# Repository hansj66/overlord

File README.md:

# Overlord Robot Controller

## Overview

"Overlord" is a carrier board for the Raspberry Pi Compute module 5. The board facilitates easy integration with [Xiaomi Cybergear](https://www.mi.com/cyber-gear) motors and half duplex Dynamixels, like the [AX-12A](https://emanual.robotis.com/docs/en/dxl/ax/ax-12a/), [MX-12W](https://emanual.robotis.com/docs/en/dxl/ax/ax-12a/) servos.

The carrier board has an onboard can controller, can transciever, a 9 axis IMU with 100Hz sensor fusion, half duplex line driver circuitry for Dynamixel servos and has an acceptable power input range from 5 to 36V.

This repository contains:
* All the necessary KiCad schematics, PCB layout and gerber files for making copies of the carrier board.
* boot/firmware/config.txt (for the necessary boot overlays and IO mappings).
* Go code examples for communicating with Dynamixels, Cybergears and the IMU.
* Go code examples for how to implement remote control via a bluetooth gamepad, FrSky [XSR-SIM](https://www.frsky-rc.com/product/xsr-sim/) (or similar HID device).

## Licensing
This is open hardware and software. Licensing terms can be found [here](LICENSE.md).

## Getting started

In addition to the carrier board, you will need a 
* [Compute module 5](https://datasheets.raspberrypi.com/cm5/cm5-datasheet.pdf). 
* [Raspberry Pi Development Kit for Compute Module 5](https://www.raspberrypi.com/products/cm5-dev-kit/)
* If you plan to use wifi, I strongly suggest getting the official Raspberry Pi Compute module 4/5 antenna kit.
* A passive or active cooler for the CM5. If using an active cooler, attach the FAN connector to the "COOLER" socket on the carrier board.

### Programming the CM5

1. The compute module has to be flashed with an operating system before it can be used. Information on how to do this is available in the ["Compute Module Hardware"](https://www.raspberrypi.com/documentation/computers/compute-module.html#flash-compute-module-emmc) section on the offical [raspberrypi.com](https://www.raspberrypi.com/) site. Remember to enable SSH in the OS customisation settings before flashing the module.
1. Mount the CM5 in the carrier board and attach a battery or power supply to the "COMPUTE POWAH" port. Observe polarity. There is no reverse polarity protection circuitry. Reversing polarity will in all likelyhood fry the carrier board.
1. The blue LED on the carrier board will light up, indicating that it has 5V power. 
1. The CM5 will require a few seconds to boot before you can ssh in. (Tip: create an .ssh folder under the CM5 home folder and copy your public key to ./ssh/authorized_keys. You can then "ssh hostname" without having to type in a password)
1. The compute module will announce itself on the network. Given a "hostname", you should now be able to "ssh hostname" to get shell access.
1. Once you have shell access, run "sudo raspi-config" to enable i2c, spi and UART (enable serial port hardware, but not serial shell).
1. Now you can "sudo vi /boot/firmware/config.txt. Update the config.txt according to the [config.txt](./config/config.txt) in this repository. 
1. Run "sudo reboot now" to reboot the module. This makes sure that the correct overlays are loaded and that the GPIO mappings are correct.

You are now all set to start playing around with the board.

## Configuration and code examples

* [Remote control](./firmware/examples/remote-control/README.md)
* [Dynamixel](./firmware/examples/dynamixel/README.md)
* [Xiaomi Cybergear](./firmware/examples/cybergear/README.MD)
* [IMU](./firmware/examples/imu/README.md)

## Networking

This board was designed for simplicity and ease of use with the primary goal being actuator control and balancing. Apart from the onboard IMU, there is no sensing or GPIO access. It is however possible to directly connect the board to another Pi or any other board that supports Auto MDI-X directly using a standard ethernet cable. Access to GPIO, camera etc can then be implemented via a simple tcp client/server.

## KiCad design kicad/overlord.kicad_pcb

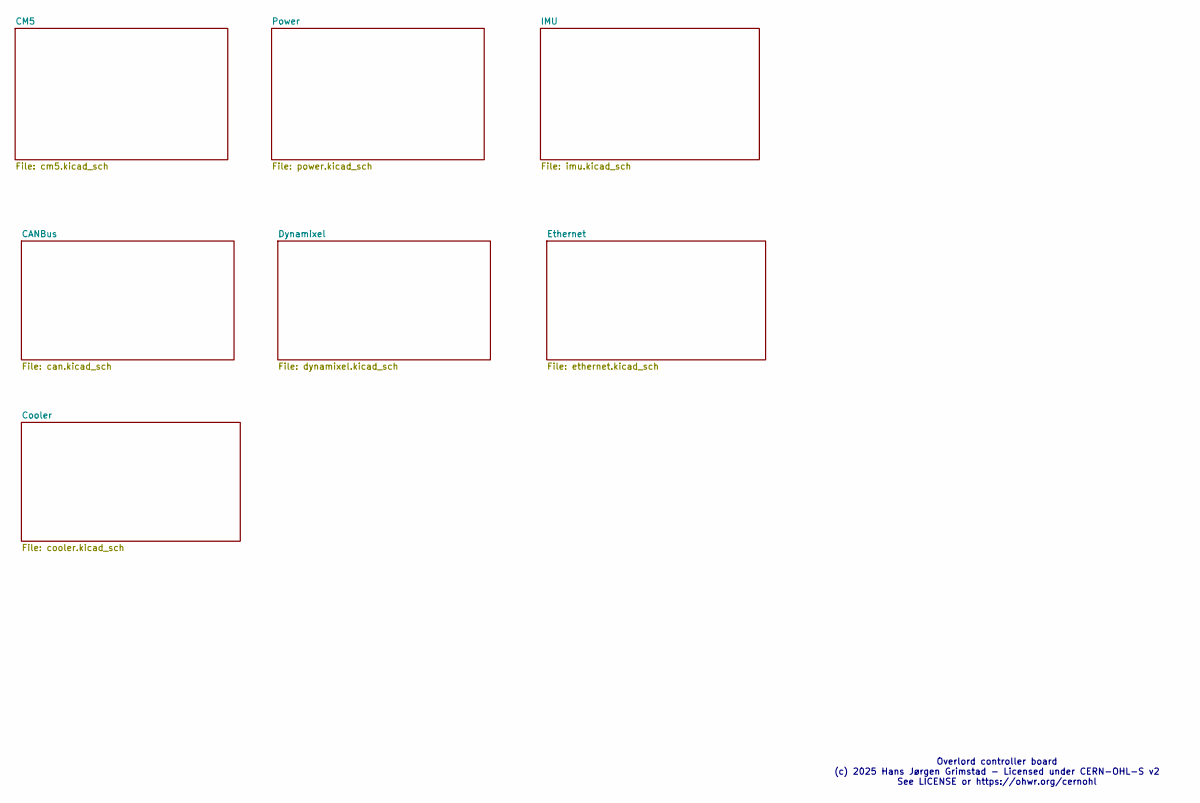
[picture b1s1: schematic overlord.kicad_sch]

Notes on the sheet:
Overlord controller board (c) 2025 Hans Jørgen Grimstad - Licensed under CERN-OHL-S v2 See LICENSE or https://ohwr.org/cernohl

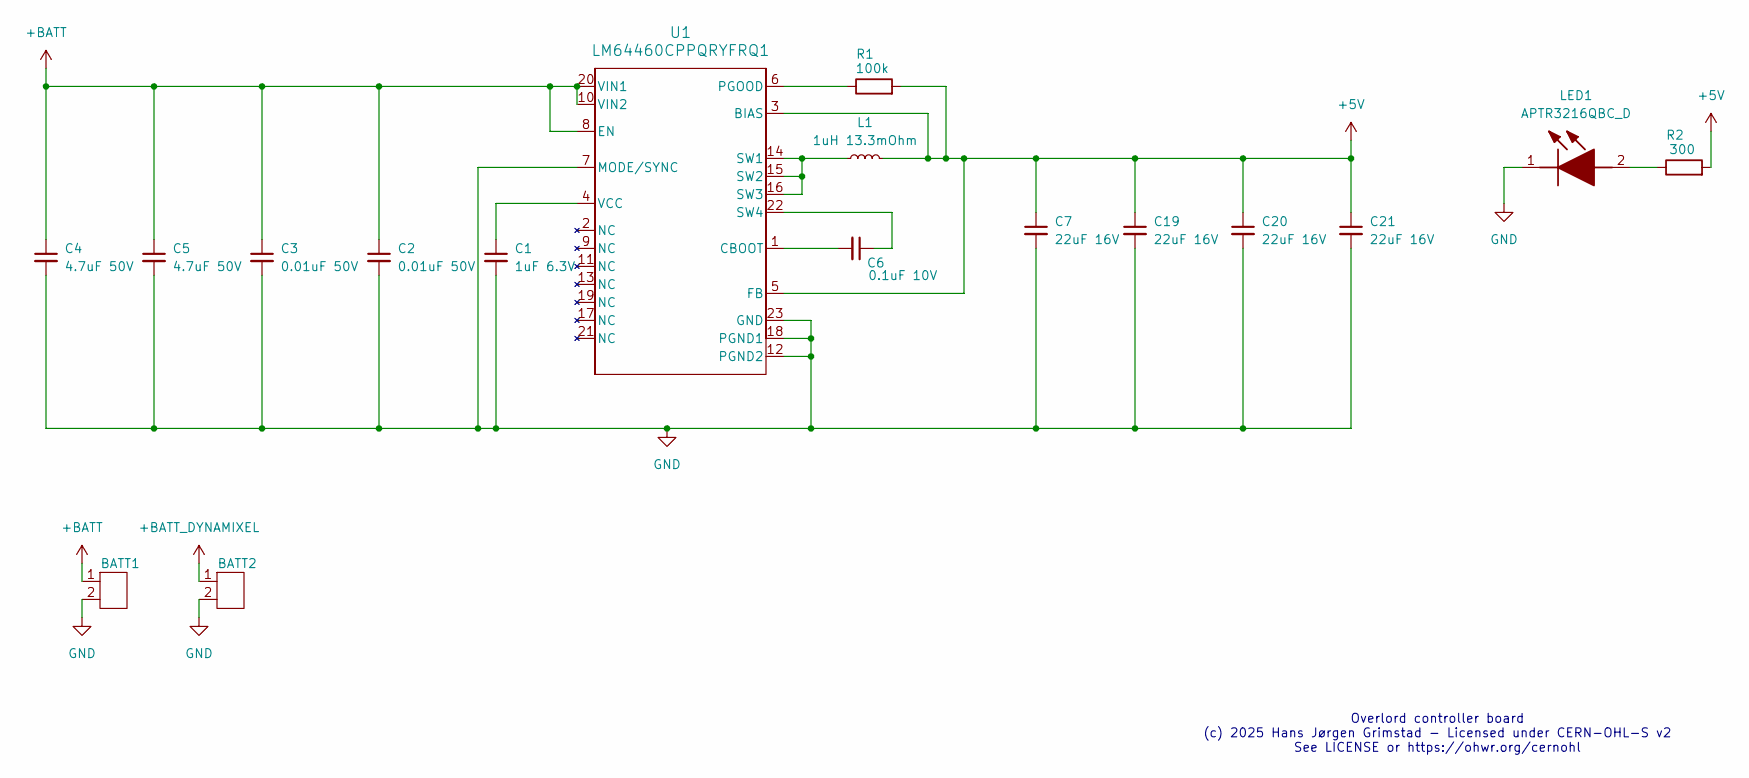
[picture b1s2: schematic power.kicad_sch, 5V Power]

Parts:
BATT1, BATT2: MOLEX-39531-5002
C1: 1uF 6.3V; C_0603_1608Metric
C2, C3: 0.01uF 50V; C_0402_1005Metric
C4, C5: 4.7uF 50V; C_1206_3216Metric
C6: 0.1uF 10V; C_0402_1005Metric
C7, C19, C20, C21: 22uF 16V; C_1210_3225Metric
L1: 1uH 13.3mOhm; L_Coilcraft_XAL4020-XXX
LED1: APTR3216QBC_D; LED_1206_3216Metric; Mouser Part Number 604-APTR3216QBC/D
R1: 100k; R_0402_1005Metric
R2: 300; R_0402_1005Metric
U1: LM64460CPPQRYFRQ1; VQFN22_RYF_TEX

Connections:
+5V: C7.1, C19.1, C20.1, C21.1, L1.2, R1.2, R2.2, U1.3 (BIAS), U1.5 (FB); also elsewhere on the board
+BATT: BATT1.1, C2.1, C3.1, C4.1, C5.1, U1.8 (EN), U1.10 (VIN2), U1.20 (VIN1)
+BATT_DYNAMIXEL: BATT2.1; also elsewhere on the board
GND: BATT1.2, BATT2.2, C1.2, C2.2, C3.2, C4.2, C5.2, C7.2, C19.2, C20.2, C21.2, U1.7 (MODE/SYNC), U1.12 (PGND2), U1.18 (PGND1), U1.23 (GND); also elsewhere on the board
unnamed 35: LED1.2 (A), R2.1; also elsewhere on the board
unnamed: C6.2, U1.1 (CBOOT)
unnamed: R1.1, U1.6 (PGOOD)
unnamed: L1.1, U1.14 (SW1), U1.15 (SW2), U1.16 (SW3)
unnamed: C6.1, U1.22 (SW4)
unnamed: C1.1, U1.4 (VCC)

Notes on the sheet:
Overlord controller board (c) 2025 Hans Jørgen Grimstad - Licensed under CERN-OHL-S v2 See LICENSE or https://ohwr.org/cernohl

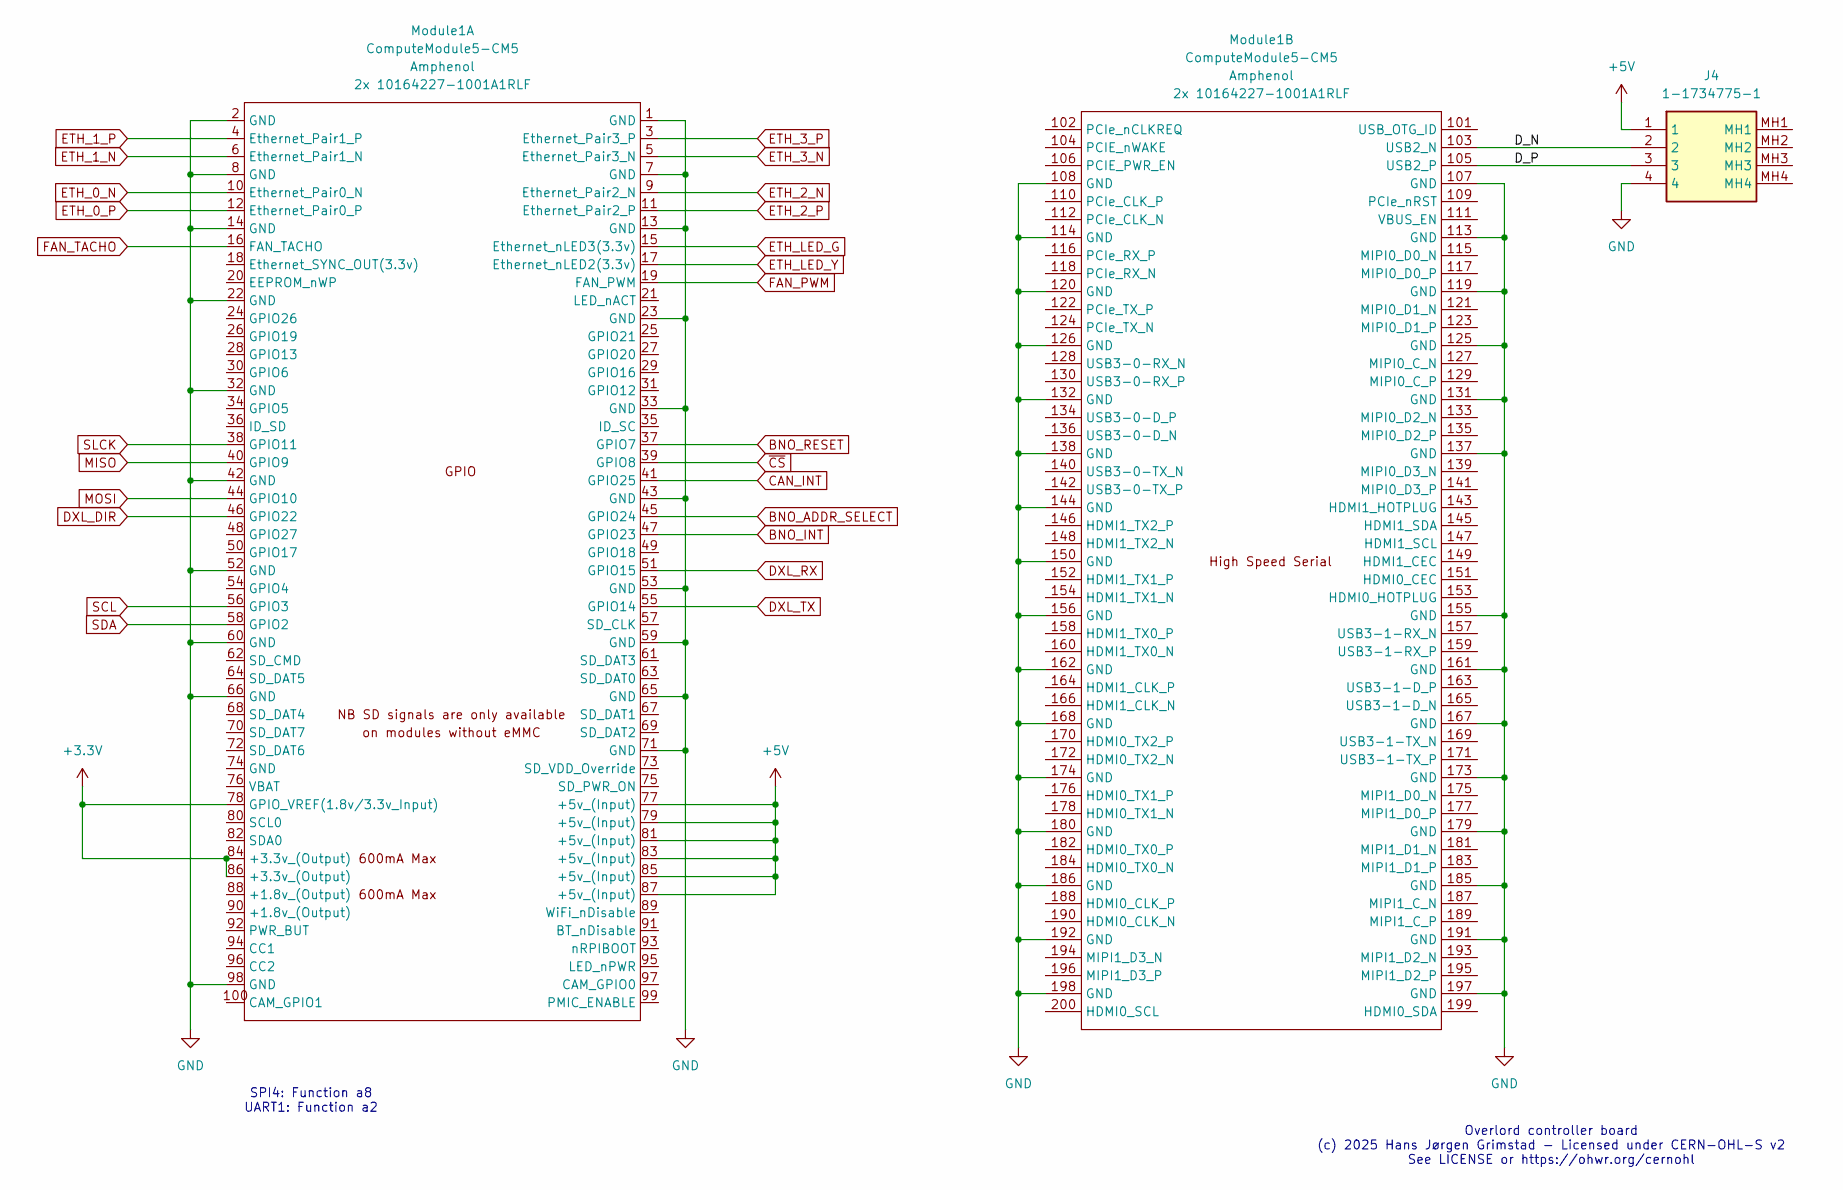
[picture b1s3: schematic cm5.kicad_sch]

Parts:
J4: 1-1734775-1; 117347751; Mouser Part Number 571-1-1734775-1
Module1: ComputeModule5-CM5; Raspberry-Pi-5-Compute-Module

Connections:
+3.3V: Module1.78 (GPIO_VREF(1.8v/3.3v_Input)), Module1.84 (+3.3v_(Output)), Module1.86 (+3.3v_(Output)); also elsewhere on the board
+5V: J4.1, Module1.77 (+5v_(Input)), Module1.79 (+5v_(Input)), Module1.81 (+5v_(Input)), Module1.83 (+5v_(Input)), Module1.85 (+5v_(Input)), Module1.87 (+5v_(Input)); also elsewhere on the board
/CM5/DN: J4.3, Module1.105 (USB2_P)
/CM5/DP: J4.2, Module1.103 (USB2_N)
BNO_ADDR_SELECT: Module1.45 (GPIO24); also elsewhere on the board
BNO_INT: Module1.47 (GPIO23); also elsewhere on the board
BNO_RESET: Module1.37 (GPIO7); also elsewhere on the board
CAN_INT: Module1.41 (GPIO25); also elsewhere on the board
DXL_DIR: Module1.46 (GPIO22); also elsewhere on the board
DXL_RX: Module1.51 (GPIO15); also elsewhere on the board
DXL_TX: Module1.55 (GPIO14); also elsewhere on the board
ETH_0_N: Module1.10 (Ethernet_Pair0_N); also elsewhere on the board
ETH_0_P: Module1.12 (Ethernet_Pair0_P); also elsewhere on the board
ETH_1_N: Module1.6 (Ethernet_Pair1_N); also elsewhere on the board
ETH_1_P: Module1.4 (Ethernet_Pair1_P); also elsewhere on the board
ETH_2_N: Module1.9 (Ethernet_Pair2_N); also elsewhere on the board
ETH_2_P: Module1.11 (Ethernet_Pair2_P); also elsewhere on the board
ETH_3_N: Module1.5 (Ethernet_Pair3_N); also elsewhere on the board
ETH_3_P: Module1.3 (Ethernet_Pair3_P); also elsewhere on the board
ETH_LED_G: Module1.15 (Ethernet_nLED3(3.3v)); also elsewhere on the board
ETH_LED_Y: Module1.17 (Ethernet_nLED2(3.3v)); also elsewhere on the board
FAN_PWM: Module1.19 (FAN_PWM); also elsewhere on the board
FAN_TACHO: Module1.16 (FAN_TACHO); also elsewhere on the board
GND: J4.4, Module1.1 (GND), Module1.2 (GND), Module1.7 (GND), Module1.8 (GND), Module1.13 (GND), Module1.14 (GND), Module1.22 (GND), Module1.23 (GND), Module1.32 (GND), Module1.33 (GND), Module1.42 (GND), Module1.43 (GND), Module1.52 (GND), Module1.53 (GND), Module1.59 (GND), Module1.60 (GND), Module1.65 (GND), Module1.66 (GND), Module1.71 (GND), Module1.98 (GND), Module1.107 (GND), Module1.108 (GND), Module1.113 (GND), Module1.114 (GND), Module1.119 (GND), Module1.120 (GND), Module1.125 (GND), Module1.126 (GND), Module1.131 (GND), Module1.132 (GND), Module1.137 (GND), Module1.138 (GND), Module1.144 (GND), Module1.150 (GND), Module1.155 (GND), Module1.156 (GND), Module1.161 (GND), Module1.162 (GND), Module1.167 (GND), Module1.168 (GND), Module1.173 (GND), Module1.174 (GND), Module1.179 (GND), Module1.180 (GND), Module1.185 (GND), Module1.186 (GND), Module1.191 (GND), Module1.192 (GND), Module1.197 (GND), Module1.198 (GND); also elsewhere on the board
MISO: Module1.40 (GPIO9); also elsewhere on the board
MOSI: Module1.44 (GPIO10); also elsewhere on the board
SCL: Module1.56 (GPIO3); also elsewhere on the board
SDA: Module1.58 (GPIO2); also elsewhere on the board
SLCK: Module1.38 (GPIO11); also elsewhere on the board
~CS: Module1.39 (GPIO8); also elsewhere on the board

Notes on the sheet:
SPI4: Function a8 UART1: Function a2
Overlord controller board (c) 2025 Hans Jørgen Grimstad - Licensed under CERN-OHL-S v2 See LICENSE or https://ohwr.org/cernohl

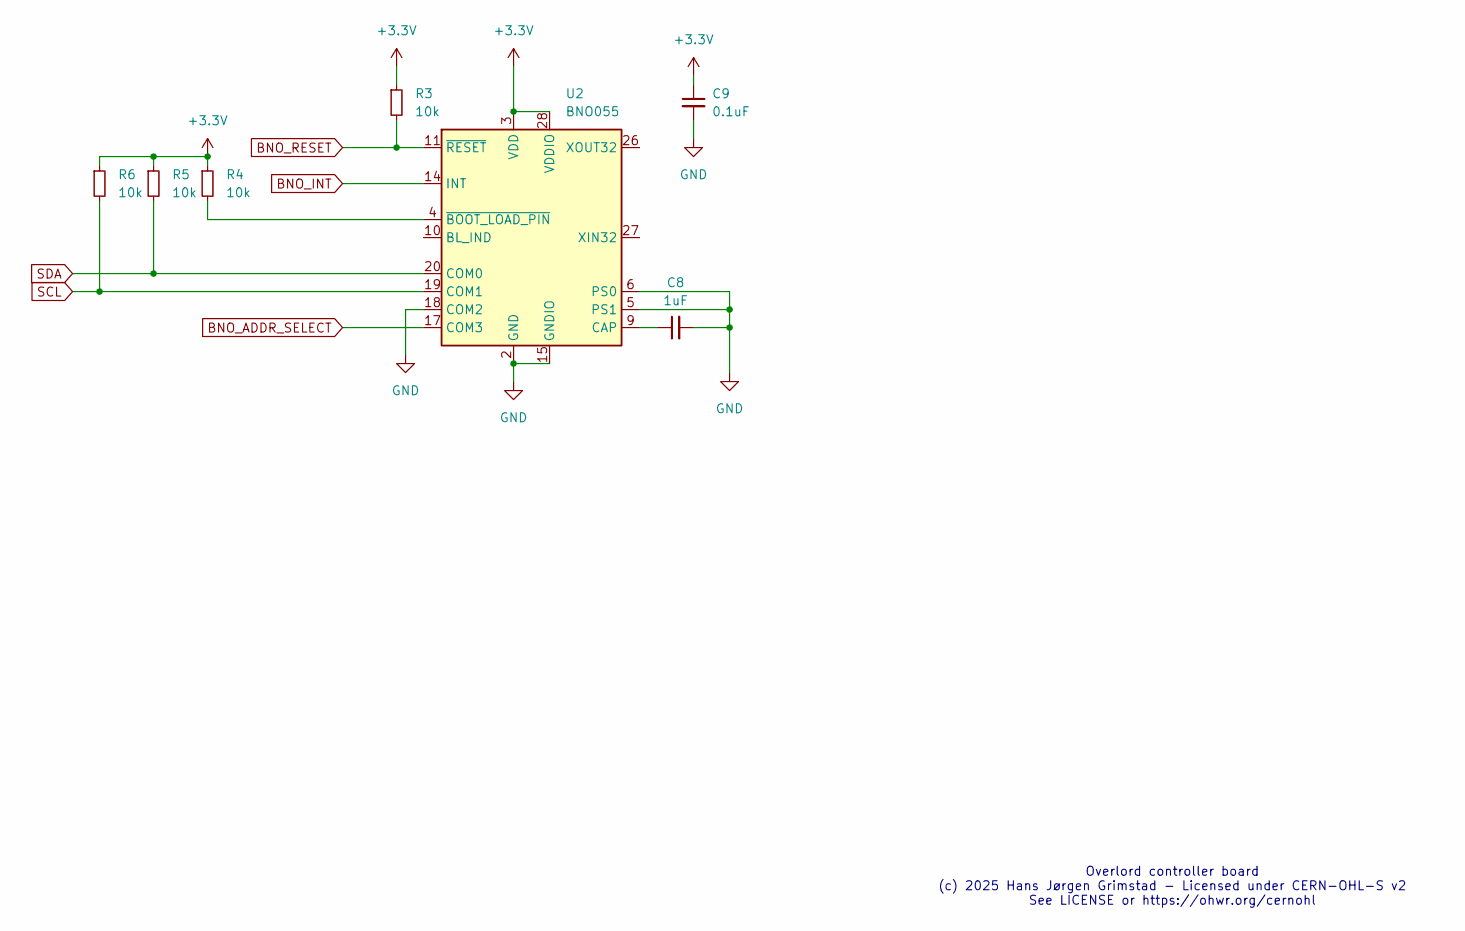
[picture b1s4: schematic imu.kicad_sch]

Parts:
C8: 1uF; C_0402_1005Metric
C9: 0.1uF; C_0402_1005Metric
R3, R4, R5, R6: 10k; R_0402_1005Metric
U2: BNO055; LGA-28_5.2x3.8mm_P0.5mm

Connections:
+3.3V: C9.1, R3.1, R4.1, R5.1, R6.1, U2.3 (VDD), U2.28 (VDDIO); also elsewhere on the board
BNO_ADDR_SELECT: U2.17 (COM3); also elsewhere on the board
BNO_INT: U2.14 (INT); also elsewhere on the board
BNO_RESET: R3.2, U2.11 (~RESET); also elsewhere on the board
GND: C8.2, C9.2, U2.2 (GND), U2.5 (PS1), U2.6 (PS0), U2.15 (GNDIO), U2.16 (GNDIO), U2.18 (COM2), U2.25 (GNDIO); also elsewhere on the board
unnamed: C8.1, U2.9 (CAP)
unnamed: R4.2, U2.4 (~BOOT_LOAD_PIN)
SCL: R6.2, U2.19 (COM1); also elsewhere on the board
SDA: R5.2, U2.20 (COM0); also elsewhere on the board

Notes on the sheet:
Overlord controller board (c) 2025 Hans Jørgen Grimstad - Licensed under CERN-OHL-S v2 See LICENSE or https://ohwr.org/cernohl

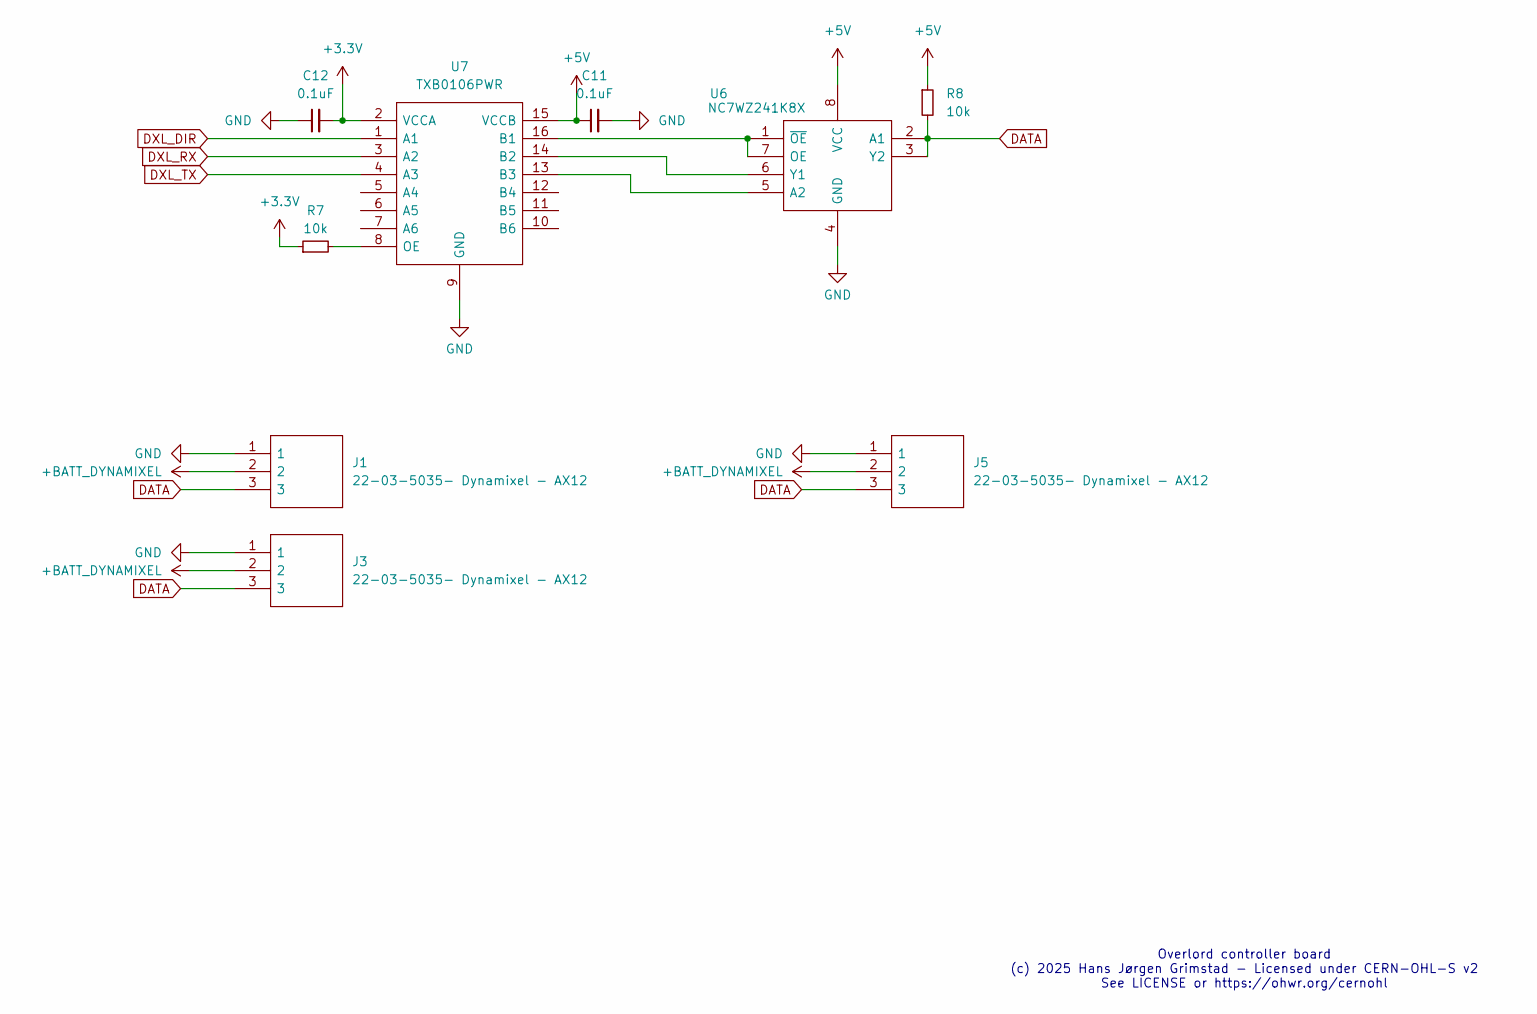
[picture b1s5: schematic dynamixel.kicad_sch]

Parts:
C11, C12: 0.1uF; C_0603_1608Metric
J1, J3, J5: 22-03-5035- Dynamixel - AX12; SHDR3W60P0X250_1X3_990X490X590P; Mouser Part Number 538-22-03-5035
R7, R8: 10k; R_0402_1005Metric
U6: NC7WZ241K8X; SOP50P310X90-8N; Mouser Part Number 512-NC7WZ241K8X
U7: TXB0106PWR; SOP65P640X120-16N; Mouser Part Number 595-TXB0106PWR

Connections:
+3.3V: C12.2, R7.1, U7.2 (VCCA); also elsewhere on the board
+5V: C11.1, R8.1, U6.8 (VCC), U7.15 (VCCB); also elsewhere on the board
+BATT_DYNAMIXEL: J1.2, J3.2, J5.2; also elsewhere on the board
DATA: J1.3, J3.3, J5.3, R8.2, U6.2 (A1), U6.3 (Y2)
DXL_DIR: U7.1 (A1); also elsewhere on the board
DXL_RX: U7.3 (A2); also elsewhere on the board
DXL_TX: U7.4 (A3); also elsewhere on the board
GND: C11.2, C12.1, J1.1, J3.1, J5.1, U6.4 (GND), U7.9 (GND); also elsewhere on the board
unnamed: U6.5 (A2), U7.13 (B3)
unnamed: U6.1 (~OE), U6.7 (OE), U7.16 (B1)
unnamed: U6.6 (Y1), U7.14 (B2)
unnamed: R7.2, U7.8 (OE)

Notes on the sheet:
Overlord controller board (c) 2025 Hans Jørgen Grimstad - Licensed under CERN-OHL-S v2 See LICENSE or https://ohwr.org/cernohl

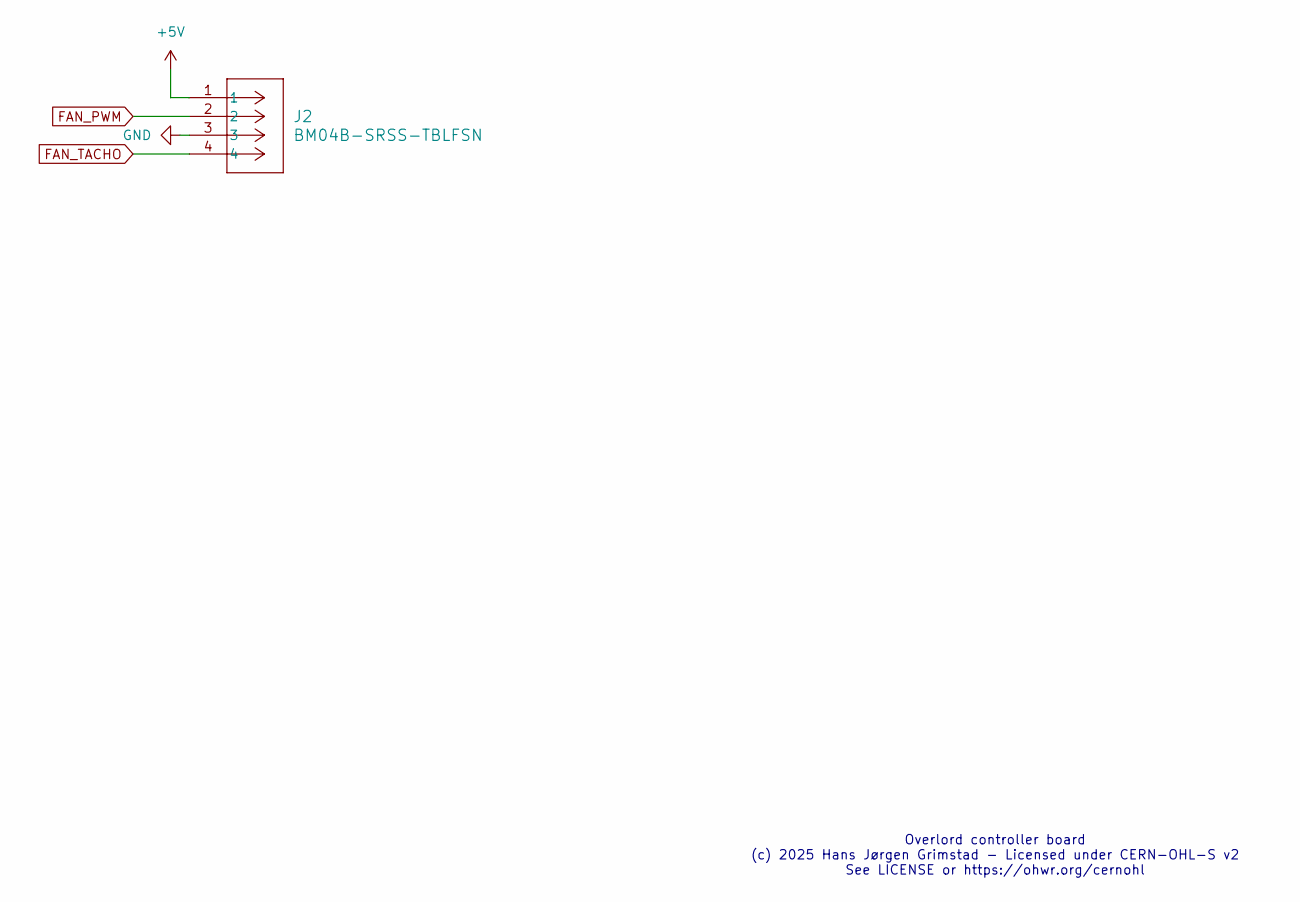
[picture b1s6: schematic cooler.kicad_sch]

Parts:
J2: BM04B-SRSS-TBLFSN; CONN4_BM04B-SRSS_JST

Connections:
+5V: J2.1; also elsewhere on the board
FAN_PWM: J2.2; also elsewhere on the board
FAN_TACHO: J2.4; also elsewhere on the board
GND: J2.3; also elsewhere on the board

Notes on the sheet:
Overlord controller board (c) 2025 Hans Jørgen Grimstad - Licensed under CERN-OHL-S v2 See LICENSE or https://ohwr.org/cernohl

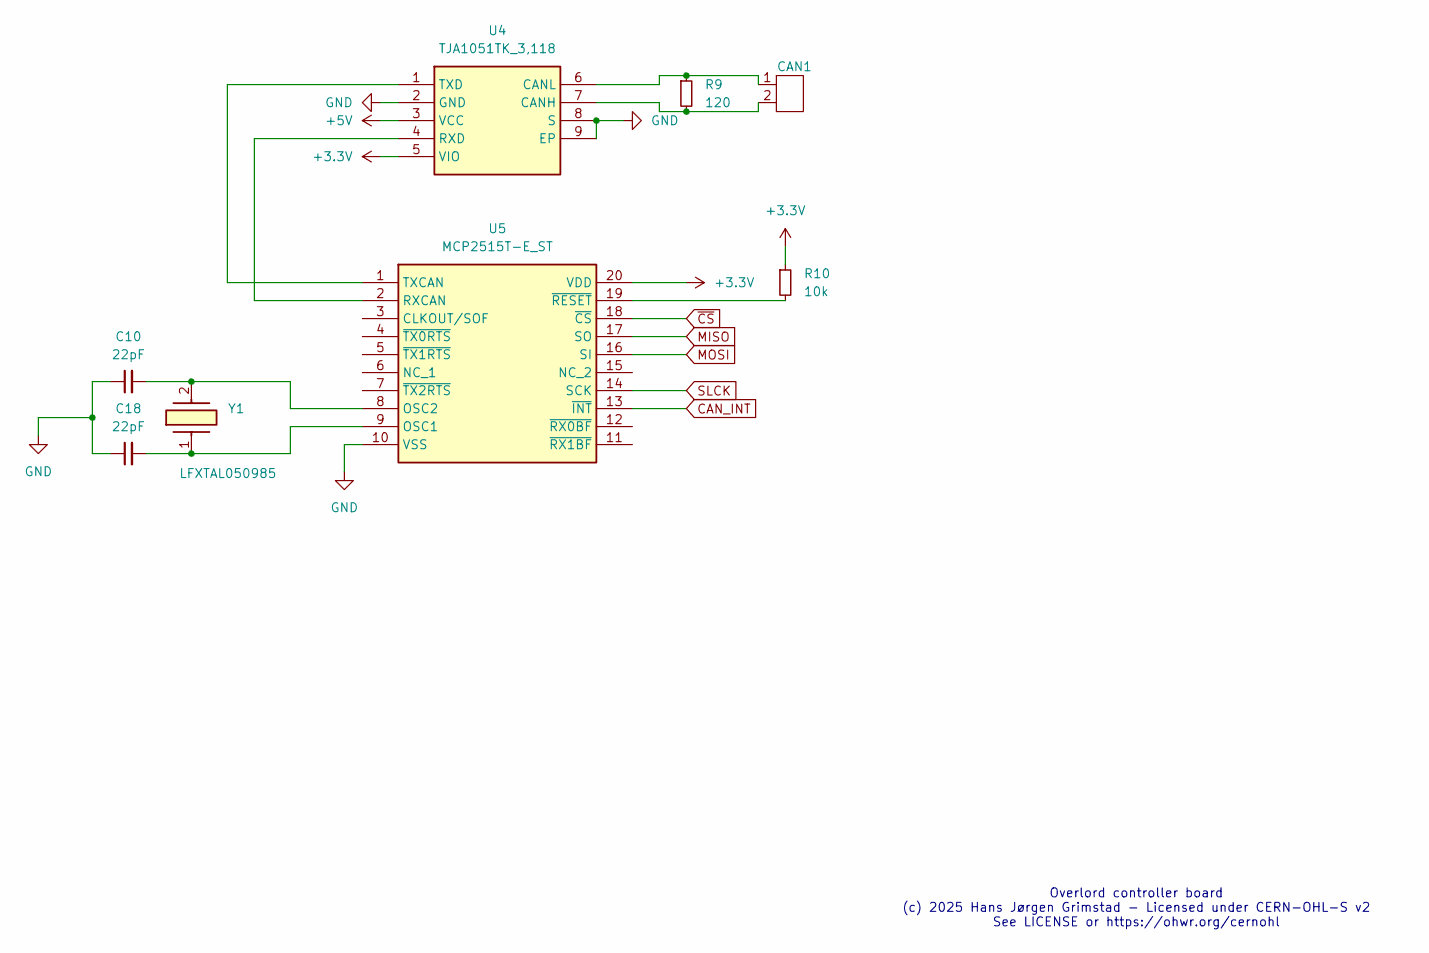
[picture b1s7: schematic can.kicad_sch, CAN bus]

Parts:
C10, C18: 22pF; C_0402_1005Metric
CAN1: MOLEX-39531-5002
R9: 120; R_1218_3246Metric
R10: 10k; R_0402_1005Metric
U4: TJA1051TK_3,118; HVSON-8-1EP_3x3mm_P0.65mm_EP1.6x2.4mm; Mouser Part Number 771-TJA1051TK/3118
U5: MCP2515T-E_ST; SOP65P640X120-20N; Mouser Part Number 579-MCP2515T-E/ST
Y1: LFXTAL050985; LFXTAL050985Bulk; Mouser Part Number 449-LFXTAL050985BULK

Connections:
+3.3V: R10.1, U4.5 (VIO), U5.20 (VDD); also elsewhere on the board
+5V: U4.3 (VCC); also elsewhere on the board
CAN_INT: U5.13 (~INT); also elsewhere on the board
GND: C10.1, C18.1, U4.2 (GND), U4.8 (S), U4.9 (EP), U5.10 (VSS); also elsewhere on the board
MISO: U5.17 (SO); also elsewhere on the board
MOSI: U5.16 (SI); also elsewhere on the board
unnamed: CAN1.2, R9.2, U4.7 (CANH)
unnamed: CAN1.1, R9.1, U4.6 (CANL)
unnamed: U4.4 (RXD), U5.2 (RXCAN)
unnamed: U4.1 (TXD), U5.1 (TXCAN)
unnamed: C18.2, U5.9 (OSC1), Y1.1
unnamed: C10.2, U5.8 (OSC2), Y1.2
unnamed: R10.2, U5.19 (~RESET)
SLCK: U5.14 (SCK); also elsewhere on the board
~CS: U5.18 (~CS); also elsewhere on the board

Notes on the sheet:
Overlord controller board (c) 2025 Hans Jørgen Grimstad - Licensed under CERN-OHL-S v2 See LICENSE or https://ohwr.org/cernohl

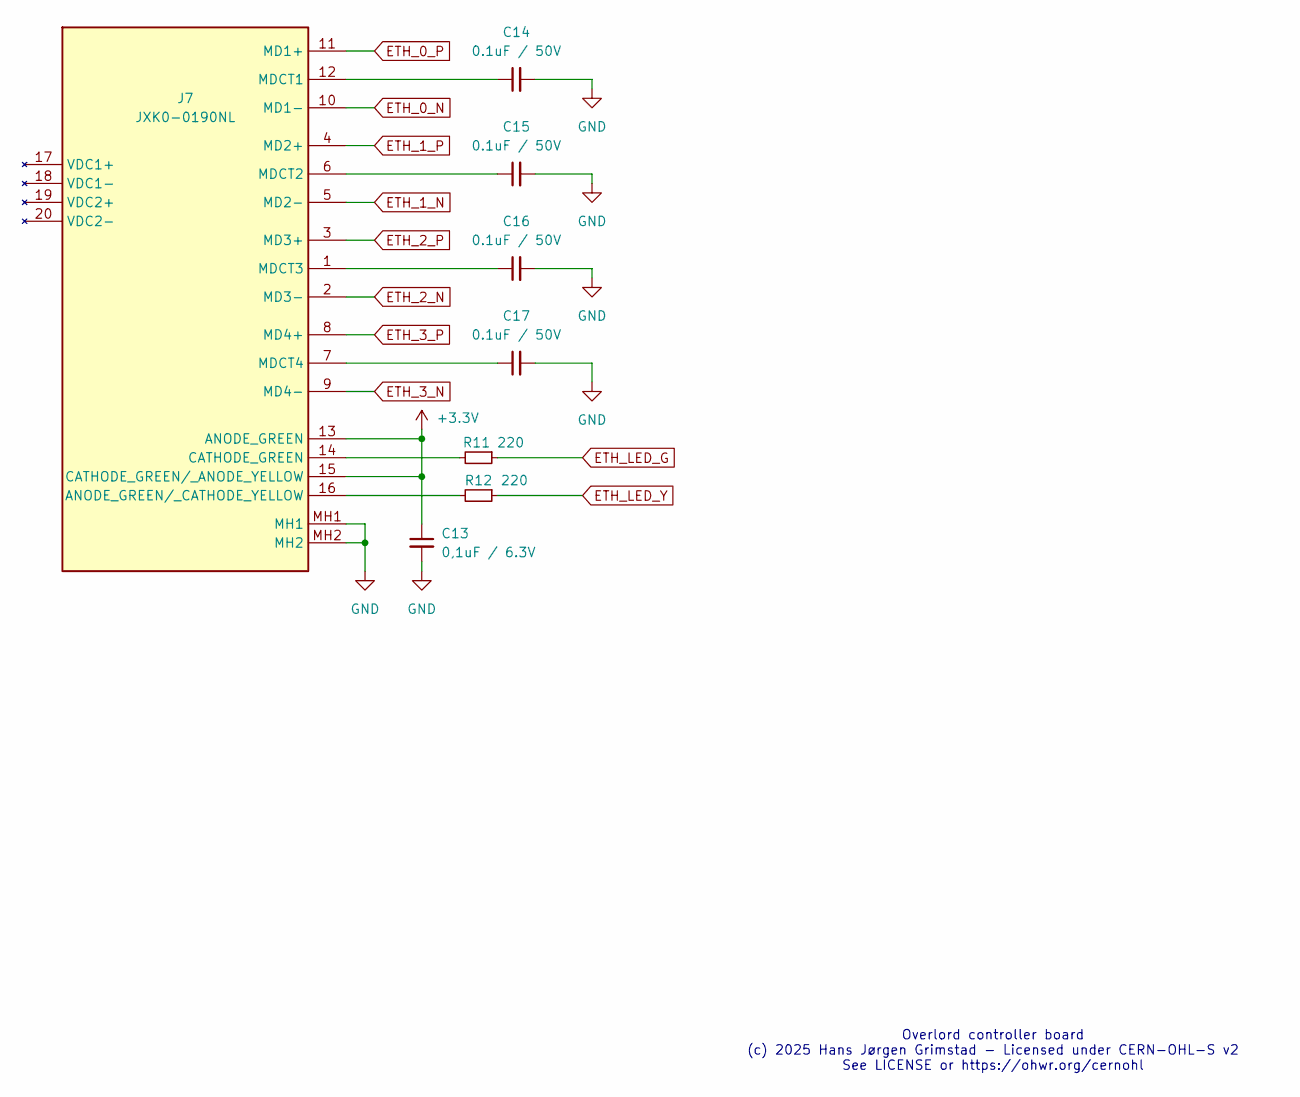
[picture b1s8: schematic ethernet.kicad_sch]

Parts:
C13: 0,1uF / 6.3V; C_0603_1608Metric
C14, C15, C16, C17: 0.1uF / 50V; C_0603_1608Metric
J7: JXK0-0190NL; CONN20_0-0190NL_PUL; Mouser Part Number 673-JXK0-0190NL
R11, R12: 220; R_0402_1005Metric

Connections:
+3.3V: C13.1, J7.13 (ANODE_GREEN), J7.15 (CATHODE_GREEN/_ANODE_YELLOW); also elsewhere on the board
ETH_0_N: J7.10 (MD1-); also elsewhere on the board
ETH_0_P: J7.11 (MD1+); also elsewhere on the board
ETH_1_N: J7.5 (MD2-); also elsewhere on the board
ETH_1_P: J7.4 (MD2+); also elsewhere on the board
ETH_2_N: J7.2 (MD3-); also elsewhere on the board
ETH_2_P: J7.3 (MD3+); also elsewhere on the board
ETH_3_N: J7.9 (MD4-); also elsewhere on the board
ETH_3_P: J7.8 (MD4+); also elsewhere on the board
ETH_LED_G: R11.1; also elsewhere on the board
ETH_LED_Y: R12.1; also elsewhere on the board
GND: C13.2, C14.2, C15.2, C16.2, C17.2, J7.MH1, J7.MH2; also elsewhere on the board
unnamed: J7.16 (ANODE_GREEN/_CATHODE_YELLOW), R12.2
unnamed: J7.14 (CATHODE_GREEN), R11.2
unnamed: C14.1, J7.12 (MDCT1)
unnamed: C15.1, J7.6 (MDCT2)
unnamed: C16.1, J7.1 (MDCT3)
unnamed: C17.1, J7.7 (MDCT4)

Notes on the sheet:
Overlord controller board (c) 2025 Hans Jørgen Grimstad - Licensed under CERN-OHL-S v2 See LICENSE or https://ohwr.org/cernohl

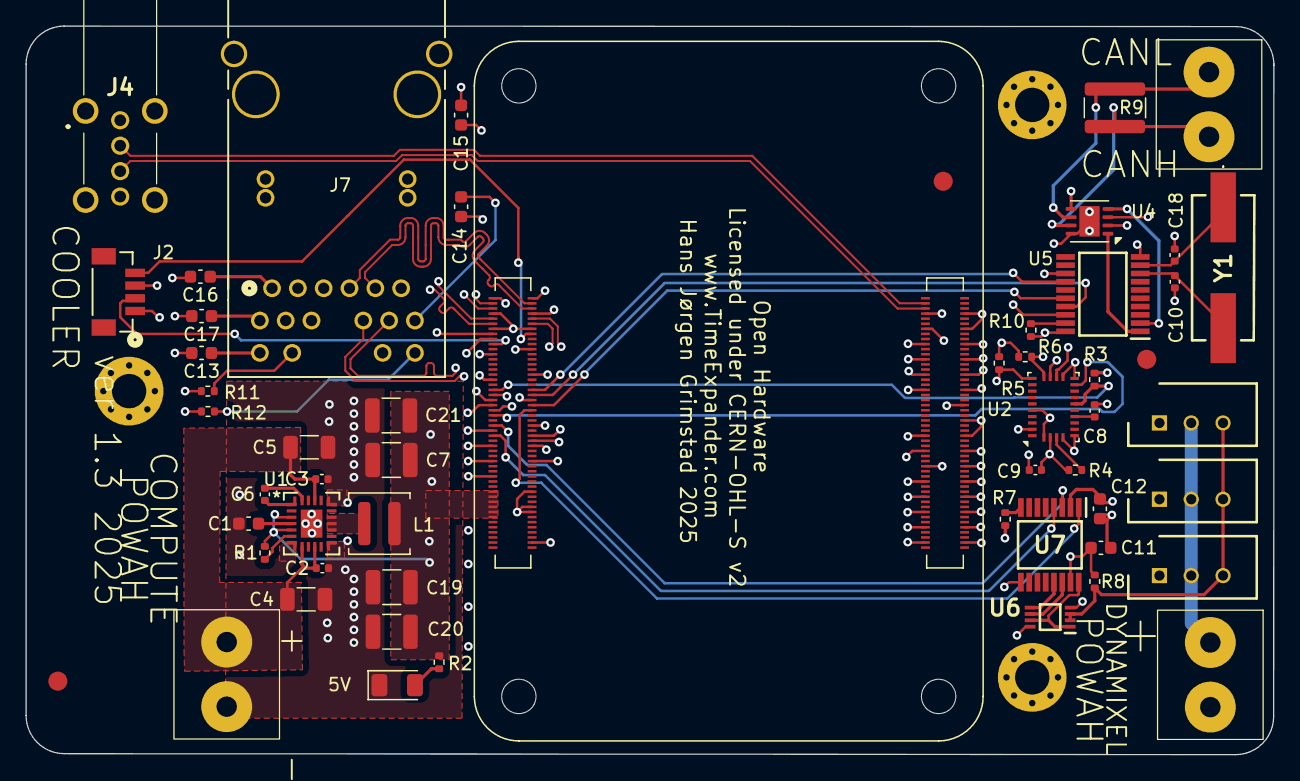
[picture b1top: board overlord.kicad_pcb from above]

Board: 6 copper layers, 98.1 x 57.3 mm, 52 parts (0 on the bottom side), 58 nets.

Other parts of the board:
5V: APTR3216QBC_D; LED_1206_3216Metric

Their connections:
GND: 5V.1 (K); also elsewhere on the board
unnamed 35: 5V.2 (A); also elsewhere on the board

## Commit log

2025-07-31 Added example code for decoding /dev/input/js0
    * Updated README
2025-08-01 Updated config.txt with correct uart overlay
2025-08-01 Added Dynamixel network scanning / protocol 1.0 example
2025-08-01 Added IMU example (chip ID + heading vector)
    * Updated various README files
2025-08-01 Updated logging in IMU example
    * Updated README
2025-08-05 Added CAN example code for cybergear
    * Updated various README files
2025-08-05 Removed silly ML training clause
2025-08-05 Removed old / redundant code
2025-08-05 Added PDF version of schematic
    * Added comment in schematic regarding CAN bitrate
